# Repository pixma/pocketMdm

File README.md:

# pocketMdm
A pocket router / AP / Switch, also runs with OpenWRT, A perfect Development kit for development around OpenWRT.

Current Version:
- rev D R1

Description
- 1 x WLAN
- 1 x LAN
- Battery backup for 1000mAh Li ion battery + Recharge battery functionality
- 1 x OTG
- 5 VDC, 1000mA Input rated
- UART Communication pad provided for development.
- Build around SKW 75 from Skylabs

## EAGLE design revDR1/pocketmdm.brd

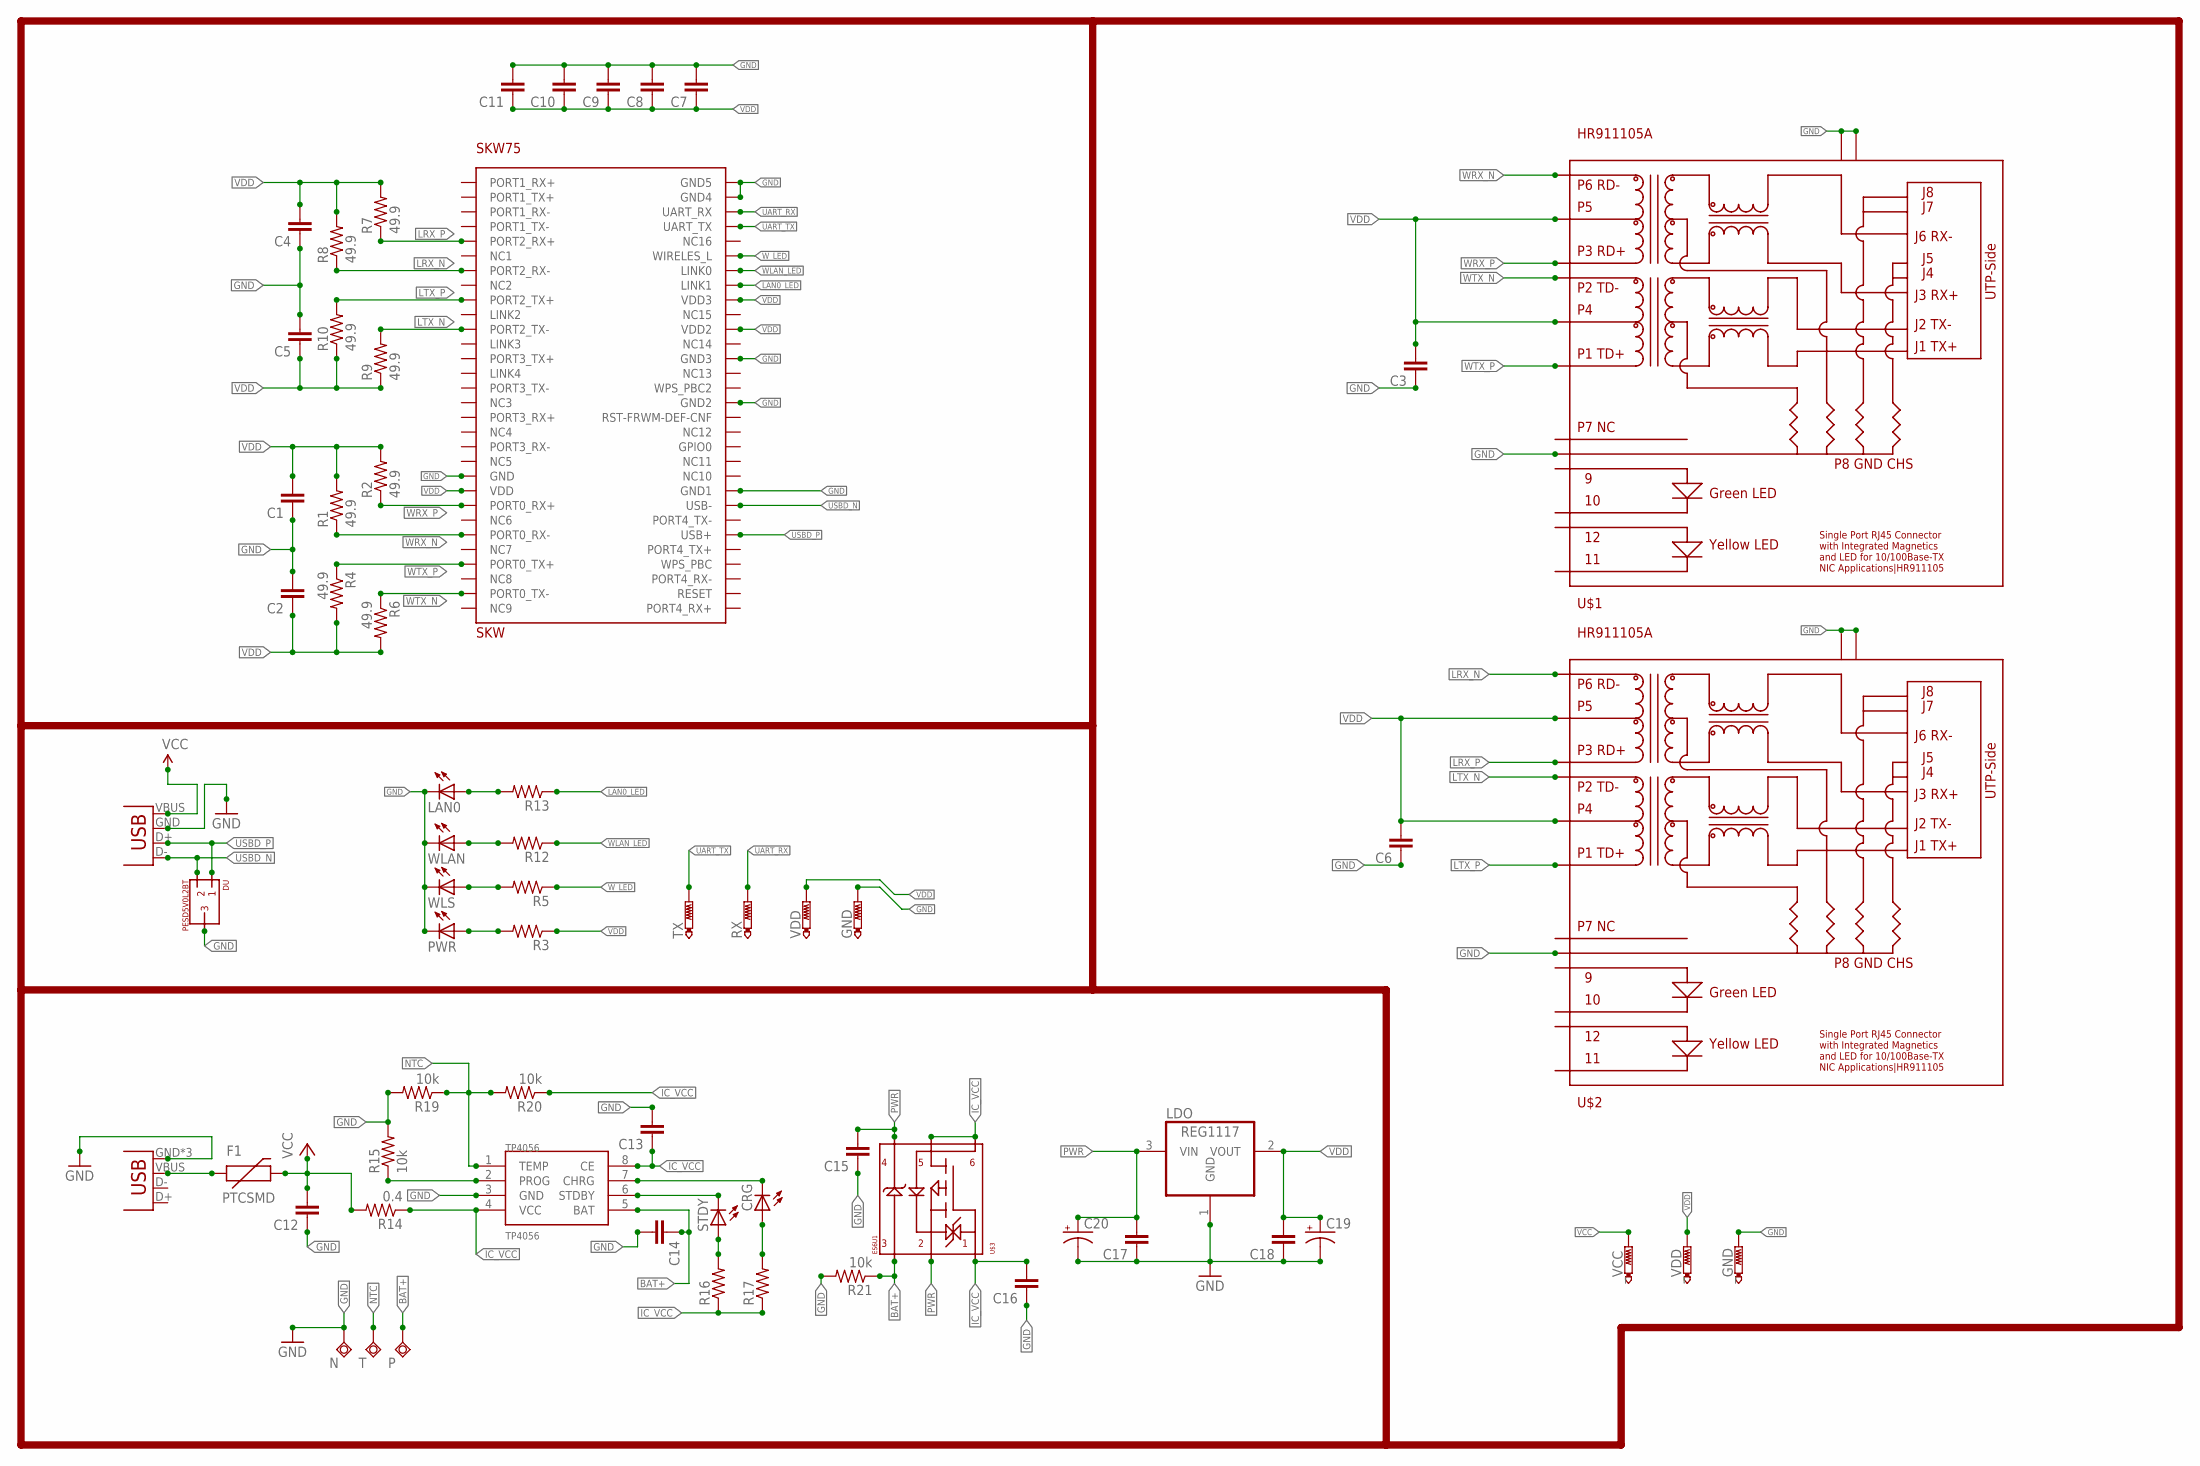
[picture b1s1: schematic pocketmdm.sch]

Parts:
C1, C2, C3, C4, C5, C6, C7, C8, C9, C10, C11, C12, C13, C14, C15, C16, C17, C18: CAP0402-CAP; 0402-CAP
C19, C20: CAP_POLPTH1; CPOL-RADIAL-100UF-25V
CRG: LEDCHIPLED_0603; CHIPLED_0603
DU: PESD5V0L2BT; SOT23
F1: PTCSMD; PTC-1206
GND: PTR1B1,27; B1,27
LAN0: LEDCHIPLED_0603; CHIPLED_0603
LDO: REG1117; SOT223
N: TPSQTP20SQ; TP20SQ
P: TPSQTP20SQ; TP20SQ
PWR: LEDCHIPLED_0603; CHIPLED_0603
R1, R2, R4, R6, R7, R8, R9, R10: 49.9; 0402-RES
R3, R5, R12, R13, R16, R17: RESISTOR0402-RES; 0402-RES
R14: 0.4; 0402-RES
R15, R19, R20, R21: 10k; 0402-RES
RX: PTR1B1,27; B1,27
SKW: SKW75; CON-60-127MMPTH
STDY: LEDCHIPLED_0603; CHIPLED_0603
T: TPSQTP20SQ; TP20SQ
TP4056: TP4056; SOP-8
TX: PTR1B1,27; B1,27
U$1, U$2: HR911105A
U$3: ES6U1; WEMT6
USBA: USB-A-H
USBM: USB-MICROB
VDD: PTR1B1,27; B1,27
WLAN: LEDCHIPLED_0603; CHIPLED_0603
WLS: LEDCHIPLED_0603; CHIPLED_0603
_GND: PTR1B1,27; B1,27
_VCC: PTR1B1,27; B1,27
_VDD: PTR1B1,27; B1,27

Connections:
BAT+: C14.1, P.TP, R21.1, TP4056.5 (BAT), U$3.P$3
GND: C1.1, C2.2, C3.1, C4.1, C5.2, C6.1, C7.2, C8.2, C9.2, C10.2, C11.2, C12.1, C13.2, C14.2, C15.1, C16.1, C17.1, C18.1, C19.2 (-), C20.2 (-), DU.3, GND.TP, LAN0.C, LDO.1 (GND), N.TP, PWR.C, R15.2, R19.2, R21.2, SKW.P$21 (GND), SKW.P$39 (GND1), SKW.P$45 (GND2), SKW.P$48 (GND3), SKW.P$59 (GND4), SKW.P$60 (GND5), TP4056.3 (GND), U$1.P$8, U$1.P$13, U$1.P$14, U$2.P$8, U$2.P$13, U$2.P$14, USBA.GND (VBUS), USBM.GND, USBM.MT1 (GND), USBM.MT2 (GND), WLAN.C, WLS.C, _GND.TP
IC_VCC: C13.1, C16.2, R14.1, R16.1, R17.1, R20.1, TP4056.4 (VCC), TP4056.8 (CE), U$3.P$1, U$3.P$5, U$3.P$6
LAN0_LED: R13.1, SKW.P$53 (LINK1)
LRX_N: R8.1, SKW.P$7 (PORT2_RX-), U$2.P$6
LRX_P: R7.1, SKW.P$5 (PORT2_RX+), U$2.P$3
LTX_N: R9.2, SKW.P$11 (PORT2_TX-), U$2.P$2
LTX_P: R10.2, SKW.P$9 (PORT2_TX+), U$2.P$1
unnamed: CRG.C, TP4056.7 (CHRG)
unnamed: F1.1, USBM.VBUS
unnamed: R15.1, TP4056.2 (PROG)
unnamed: STDY.C, TP4056.6 (STDBY)
unnamed: PWR.A, R3.2
unnamed: R5.2, WLS.A
unnamed: R12.2, WLAN.A
unnamed: R16.2, STDY.A
unnamed: CRG.A, R17.2
unnamed: LAN0.A, R13.2
NTC: R19.1, R20.2, T.TP, TP4056.1 (TEMP)
PWR: C15.2, C17.2, C20.1 (+), LDO.3 (VIN), U$3.P$2, U$3.P$4
UART_RX: RX.TP, SKW.P$58 (UART_RX)
UART_TX: SKW.P$57 (UART_TX), TX.TP
USBD_N: DU.2, SKW.P$38 (USB-), USBA.D- (D+)
USBD_P: DU.1, SKW.P$36 (USB+), USBA.D+ (D-)
VCC: C12.2, F1.2, R14.2, USBA.VBUS (GND), _VCC.TP
VDD: C1.2, C2.1, C3.2, C4.2, C5.1, C6.2, C7.1, C8.1, C9.1, C10.1, C11.1, C18.2, C19.1 (+), LDO.2 (VOUT), R1.2, R2.2, R3.1, R4.2, R6.2, R7.2, R8.2, R9.1, R10.1, SKW.P$22 (VDD), SKW.P$50 (VDD2), SKW.P$52 (VDD3), U$1.P$4, U$1.P$5, U$2.P$4, U$2.P$5, VDD.TP, _VDD.TP
WLAN_LED: R12.1, SKW.P$54 (LINK0)
WRX_N: R1.1, SKW.P$25 (PORT0_RX-), U$1.P$6
WRX_P: R2.1, SKW.P$23 (PORT0_RX+), U$1.P$3
WTX_N: R6.1, SKW.P$29 (PORT0_TX-), U$1.P$2
WTX_P: R4.1, SKW.P$27 (PORT0_TX+), U$1.P$1
W_LED: R5.1, SKW.P$55 (WIRELES_L)

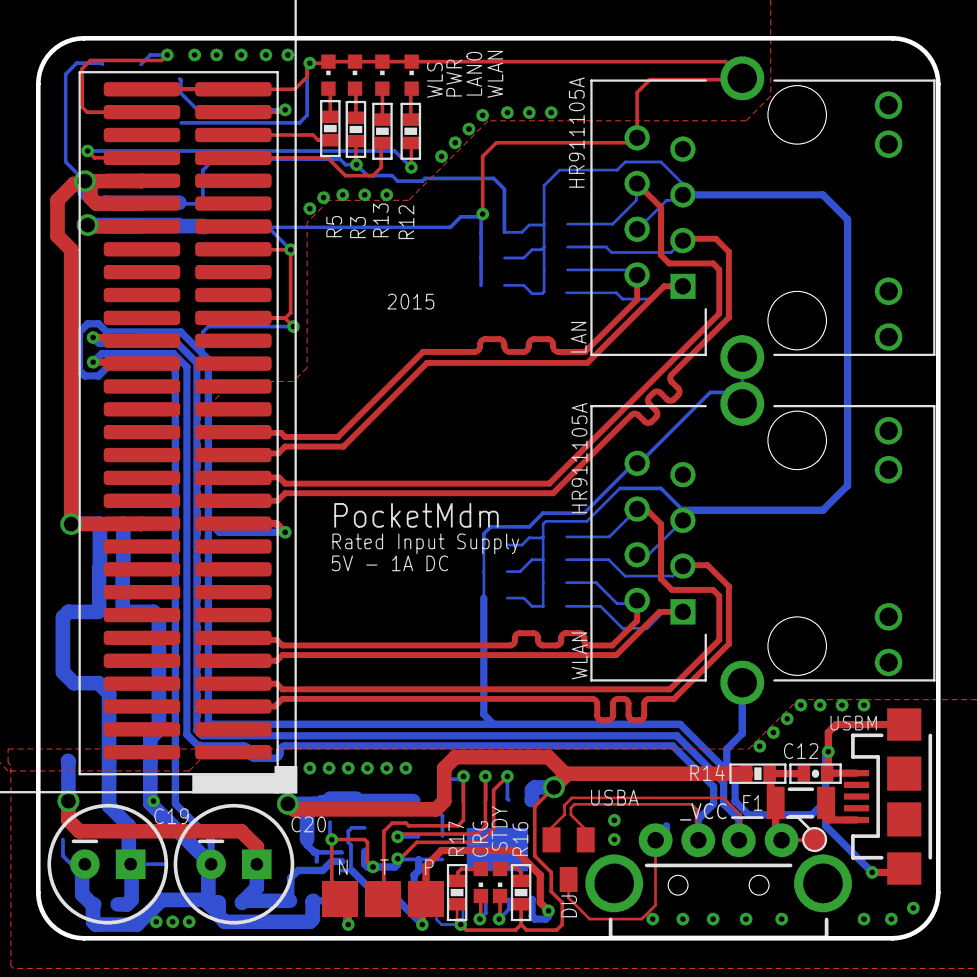
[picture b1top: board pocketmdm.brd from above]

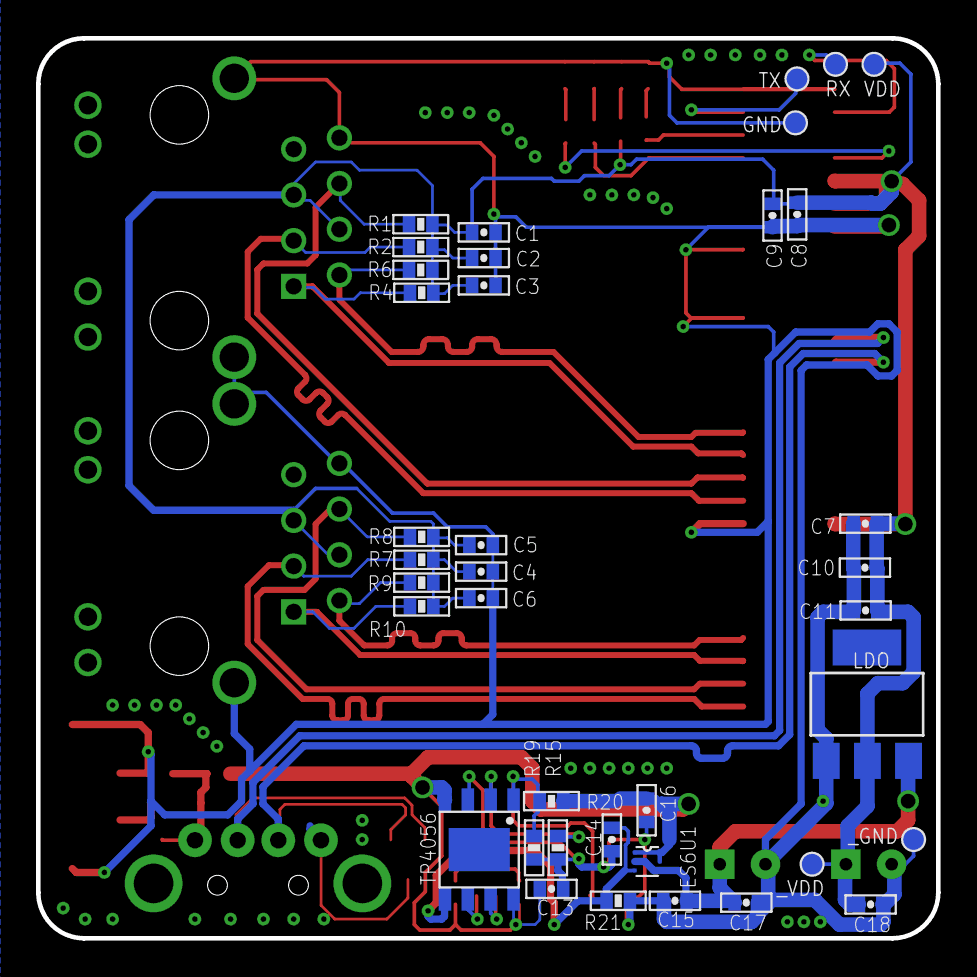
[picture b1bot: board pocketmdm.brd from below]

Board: 2 copper layers, 50.0 x 50.0 mm, 65 parts (38 on the bottom side), 32 nets.

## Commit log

2015-05-29 Wrap Up Push of Rev D-R1 version.

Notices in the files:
parts and their libraries:
SparkFun-Passives: Licensing: Creative Commons ShareAlike 4.0 International - https://creativecommons.org/licenses/by-sa/4.0
